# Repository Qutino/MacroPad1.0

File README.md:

# MacroPad1.1
This small macropad is the prototype with the intent of adding future improvements and iterating design further down the road.

Since this will be my first time building the supporting electronics around an ATMEGA32U4 microcontroller, 
as well as building and flashing the firmware from zero, a design with a smaller scope seemed like the best way to jump into things.

## Table of Contents
- [MacroPad1.1](#macropad11)
  - [Table of Contents](#table-of-contents)
  - [General Design Notes](#general-design-notes)
  - [Build Guide](#build-guide)
  - [Case Design Notes](#case-design-notes)
  - [Parts Notes](#parts-notes)
    - [HTML BOM](#html-bom)
    - [1. MCU](#1-mcu)
    - [2. Mini USB Connector](#2-mini-usb-connector)
    - [3. Fuse](#3-fuse)
    - [4. Capacitors](#4-capacitors)
    - [5. Resistors](#5-resistors)
    - [6. Reset Switch](#6-reset-switch)
    - [7. Crystal Oscillator](#7-crystal-oscillator)
    - [8. Diodes](#8-diodes)
  - [PCB Design Notes](#pcb-design-notes)
    - [Schematic](#schematic)
      - [Decoupling Capacitors](#decoupling-capacitors)
      - [Diode Matrix](#diode-matrix)
      - [Crystal Oscillator](#crystal-oscillator)
    - [Layout](#layout)
      - [Layer Count](#layer-count)
      - [Laying Traces](#laying-traces)
      - [USB Traces](#usb-traces)
      - [Decoupling capacitors](#decoupling-capacitors-1)
      - [Grounding mask](#grounding-mask)
      - [Crystal Placement](#crystal-placement)
    - [Production](#production)
      - [Surface Finish](#surface-finish)
      - [MFR](#mfr)
  - [Firmware](#firmware)
  - [Future Improvements](#future-improvements)

## General Design Notes

- Switches
  - This macropad will house 6 mechanical keyswitches, typical MX style and size.
- Dimensions
  - The PCB is 76.66mm x 42.86mm (LxW) with a notch protruding for the USB connector
  - For case designers, more detailed dimensions can be found [Here](KiCad/MacroPad1.0/MacroPad1.1_dims0.pdf) in the KiCad folder.
- Mounting
  - No holes in the PCB means the design is reliant on the plate be the main mounting structure. Either using screw holes or a sandwiched gasket mount design.
  - This is usually preferred in order to decrease the mechanical stress on the PCB itself during operation.
  - Next time include at least *one* hole in the PCB, for emergencies.
- MCU
  - ATMEGA32U4-AUR Microcontroller
  - This variant is actually rather large. for the next iteration thinking about going with the smaller MU variant, which comes in a VQFN package, 7x7mm. This will be more challenging to solder, especially without hot air or solder paste.
- USB Connection
  - Mini USB Connector
  - This is the easiest USB connector to hand solder, due to the size of the pins. good for a first prototype, but I'd like to move toward a more modern connector ASAP.
- Current protection
  - 500mA fuse
- Voltage protection
  - None, reverse voltage protection may have been a good add...

## Build Guide
- I'll create a step by step guide in a different doc soon!

## Case Design Notes
- Coming soon

## Parts Notes

### [HTML BOM](KiCad/MacroPad1.0/bom/MacroPad1.1-BOM.html)

### 1. MCU
  - [ATMEGA32U4-AUR](https://www.digikey.com/en/products/detail/microchip-technology/ATMEGA32U4-AUR/2238241)
  - 44 TQFP Package (10x10mm)
  - easy to solder
    
### 2. Mini USB Connector
  - Molex [0548190589](https://www.digikey.com/en/products/detail/molex/0548190589/2421468)
  - CONN RCPT MINI USB B 5POS SMD RA
  - 5 pin USB, easy to solder

### 3. Fuse
  - [Bel Fuse Inc. C1F 500](https://www.digikey.com/en/products/detail/bel-fuse-inc/C1F-500/4968258)
  - 1206 SMD
  - 500mA fast acting
### 4. Capacitors
  -  0805 SMD
  - 10uF, 0.1uF, 1uF, ~14pF
  - The values marked for C2 and C3 in the HTML BOM are incorrect. if not already updated, these should be replaced with 14pF capacitors. More details in the Crystal section.
### 5. Resistors
  - 0805 SMD
  - 10k: pu/pd resistors
  - 22ohm: USB datalines tx/rx.
### 6. Reset Switch
  - [PTS526 SK15 SMTR2 LFS](https://www.digikey.com/en/products/detail/c-k/PTS526-SK15-SMTR2-LFS/10056626)
  - SPST switch
  - low profile, nice form factor
### 7. Crystal Oscillator
  - [ECS-160-9-33B-CWN-TR](https://www.digikey.com/en/products/detail/ecs-inc/ECS-160-9-33B-CWN-TR/12349449)
  - 16MHz
  - Fragile, be careful when soldering! Use hot air + solder paste if available.
  - Pinout
    - There is a chamfer on the one of the pads underneath the crystal. This identifies pad #1. 
    - Pads #1 and #3 are connected to the two sides of the crystal. Pads #2 and #4 are bonded to the top metal lid and grounded.
  - Orientation
    - According to the layout, pad #1 will correspond to the bottom left pad on the pcb, on the side closest to C2.
    - The crystal is Bidirectional though, so dont worry too much about this.
### 8. Diodes
  - [1N4448W](https://www.digikey.com/en/products/detail/micro-commercial-co/1N4448W-TP/789330)
  - SOD-123 Package
  - fast switching

## PCB Design Notes

### Schematic

#### Decoupling Capacitors
- 0.1uF and 10uF decoupling capacitors are used to remove unwanted power distortion.

#### Diode Matrix
- This design implements a Diode Matrix to determine the keystrokes seen by the microcontroller.
- The Diode Matrix is what allows keyboards with 100+ keys to communicate individual keystrokes. By defining rows and columns and assigning each one to a different i/o port on the microcontroller, we can increase the number of discernable inputs to the microcontroller.
- For this board in particular, I could have mapped each Keyswitch to an individual pin on the MCU, but as more switches and features get added, we'll rapidly run out of space.
- So it's best to get used to using this early on!

#### Crystal Oscillator
- Load Capacitance: 9pF
    - The circuit was originally designed with incorrect values (1uF) chosen for the load capacitors. 
    - we can use the following equation to determine the correct values for the external load capacitors for a parallel resonant crystal.

$$ C_L = (C_{x1}*C_{x2})/(C_{x1} + C_{x2}) + C_{stray} $$

$$C_{x1} = C_{x2}$$

$$ C_x = 2(C_L - C_{stray}) $$

$$ C_L = 9pF, C_{stray} = 2pF$$

$$ \therefore C_x = 14pF$$

- Assuming a stray capacitance of 2pF, our resulting Load Capacitors C2 and C3 should be around **14pF**. (quite a lot lower than 1uF xd)
### Layout

- Initial layout:

- After optimization & improvements:
  - Slightly smaller footprint
  - Better USB Dataline routing
  - no mounting holes LOL
  - Grounding mask

#### Layer Count
- Just using a 2 layer design here, it's a simple enough design that it doesn't really require much more
- Griff recommends four layer, lets try that next time.

#### Laying Traces
- Generally speaking, I tend to like putting horizontal traces on the front side, and vertical traces on the back side of the PCB (or vice versa), connecting with vias where necessary.

#### USB Traces
- USB datalines should be parallel at all times.
- 45 degree angles for traces whenever possible, sharp corners could impact signal integrity.
- I should also have tried to avoid using vias for the USB datalines, since I've read that incorrect use could cause signal reflection and attenuation. No issues so far though!

#### Decoupling capacitors
- Placement and trace routing is important!

#### Grounding mask
- Added Grounding mask around USB, MCU, and Crystal area. 
- none around switches since that shouldn't be an area that would attract too much unwanted noise. Re-assess if possible.

#### Crystal Placement
- Crystal placed as close as reasonably possible to the XTAL pins on the MCU.
- Took care to also place Load capacitors as close to the crystal as possible.
- Long copper traces could interfere with the crystal clock. Undesirable.

### Production

#### Surface Finish
- Lead-free HASL. ENIG would have been pretty, but it's too expensive.

#### MFR
- Produced by JLCPCB, very afforable. Might consider factory population at some point.

## Firmware
- documentation coming soon

## Future Improvements
In order of most to least likely to implement

  1. More switches
  2. Hotswap sockets
  3. Power Indication LED
  5. Rotary encoder
  6. smaller MCU form factor, either VQFN ATmega32u4-MUR, or RP2040
  7. USB C connector, or at least micro USB
  8. RGB
  9. OLED display
  10. Through hole style Crystal Oscillator for easier soldering? low priority, since a smaller MCU will also be difficult to solder
  11. Bluetooth?? + Battery??

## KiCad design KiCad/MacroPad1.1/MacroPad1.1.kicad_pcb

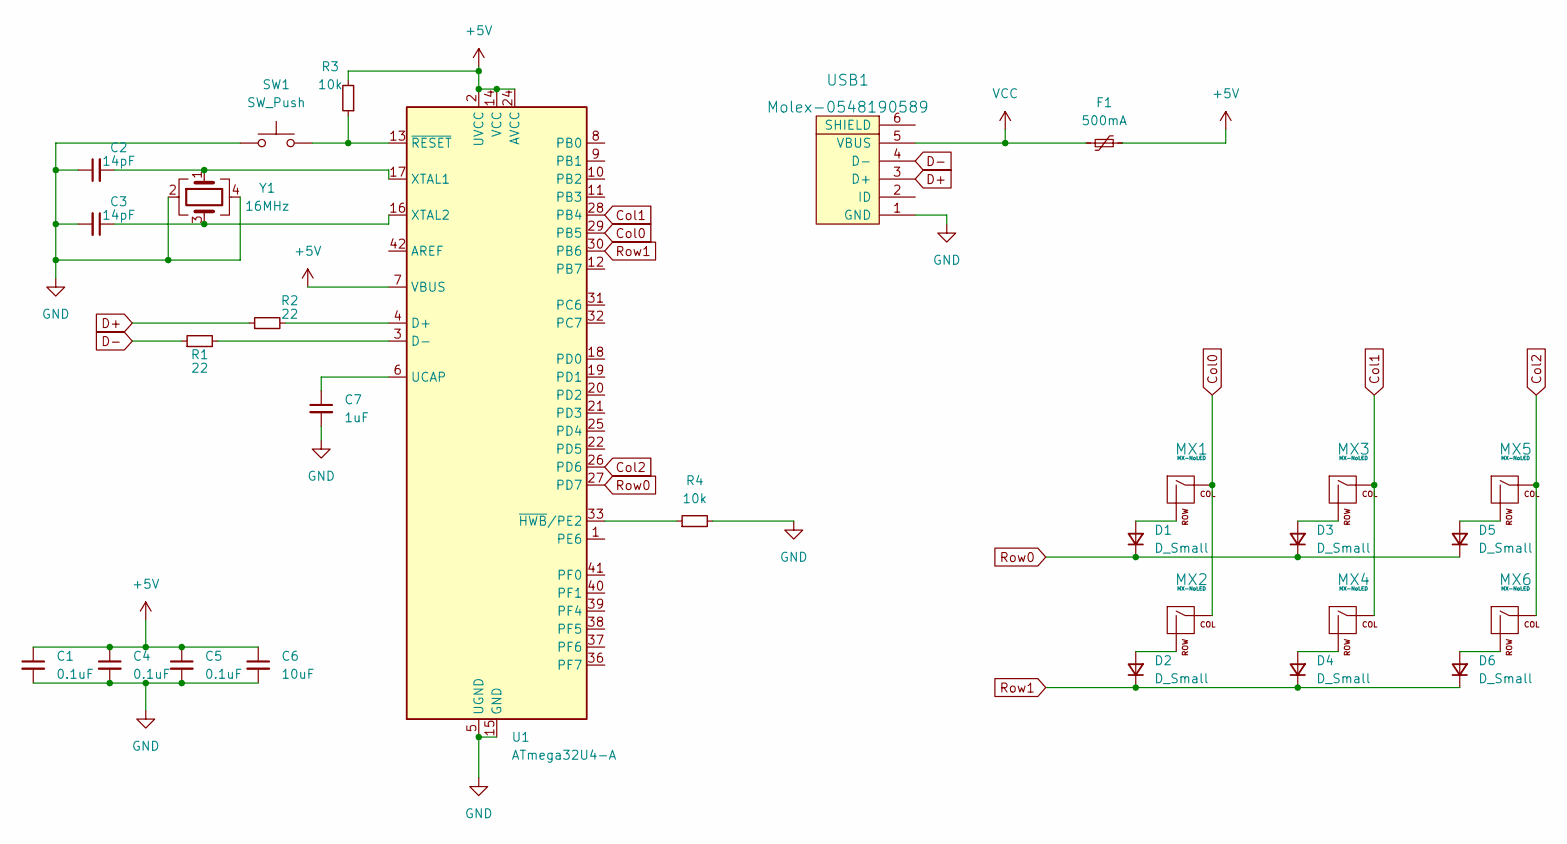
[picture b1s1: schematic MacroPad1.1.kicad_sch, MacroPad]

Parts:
C1, C4, C5: 0.1uF; C_0805_2012Metric
C2, C3: 14pF; C_0805_2012Metric
C6: 10uF; C_0805_2012Metric
C7: 1uF; C_0805_2012Metric
D1, D2, D3, D4, D5, D6: D_Small; D_SOD-123
F1: 500mA; Fuse_1206_3216Metric
MX1, MX2, MX3, MX4, MX5, MX6: MX-NoLED; MX-1U-NoLED
R1, R2: 22; R_0805_2012Metric
R3, R4: 10k; R_0805_2012Metric
SW1: SW_Push; SKQG-1155865
U1: ATmega32U4-A; TQFP-44_10x10mm_P0.8mm
USB1: Molex-0548190589
Y1: 16MHz; Crystal_SMD_3225-4Pin_3.2x2.5mm

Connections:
+5V: C1.1, C4.1, C5.1, C6.1, F1.2, R3.2, U1.2 (UVCC), U1.7 (VBUS), U1.14 (VCC), U1.24 (AVCC), U1.34 (VCC), U1.44 (AVCC)
Col0: MX1.1 (COL), MX2.1 (COL), U1.29 (PB5)
Col1: MX3.1 (COL), MX4.1 (COL), U1.28 (PB4)
Col2: MX5.1 (COL), MX6.1 (COL), U1.26 (PD6)
D+: R2.1, USB1.3 (D+)
D-: R1.1, USB1.4 (D-)
GND: C1.2, C2.1, C3.2, C4.2, C5.2, C6.2, C7.2, R4.2, SW1.1, U1.5 (UGND), U1.15 (GND), U1.23 (GND), U1.35 (GND), U1.43 (GND), USB1.1 (GND), Y1.2, Y1.4
unnamed: C2.2, U1.17 (XTAL1), Y1.1
unnamed: C3.1, U1.16 (XTAL2), Y1.3
unnamed: C7.1, U1.6 (UCAP)
unnamed: D1.2 (A), MX1.2 (ROW)
unnamed: D2.2 (A), MX2.2 (ROW)
unnamed: D3.2 (A), MX3.2 (ROW)
unnamed: D4.2 (A), MX4.2 (ROW)
unnamed: D5.2 (A), MX5.2 (ROW)
unnamed: D6.2 (A), MX6.2 (ROW)
unnamed: R1.2, U1.3 (D-)
unnamed: R2.2, U1.4 (D+)
unnamed: R3.1, SW1.2, U1.13 (~RESET)
unnamed: R4.1, U1.33 (~HWB/PE2)
Row0: D1.1 (K), D3.1 (K), D5.1 (K), U1.27 (PD7)
Row1: D2.1 (K), D4.1 (K), D6.1 (K), U1.30 (PB6)
VCC: F1.1, USB1.5 (VBUS)

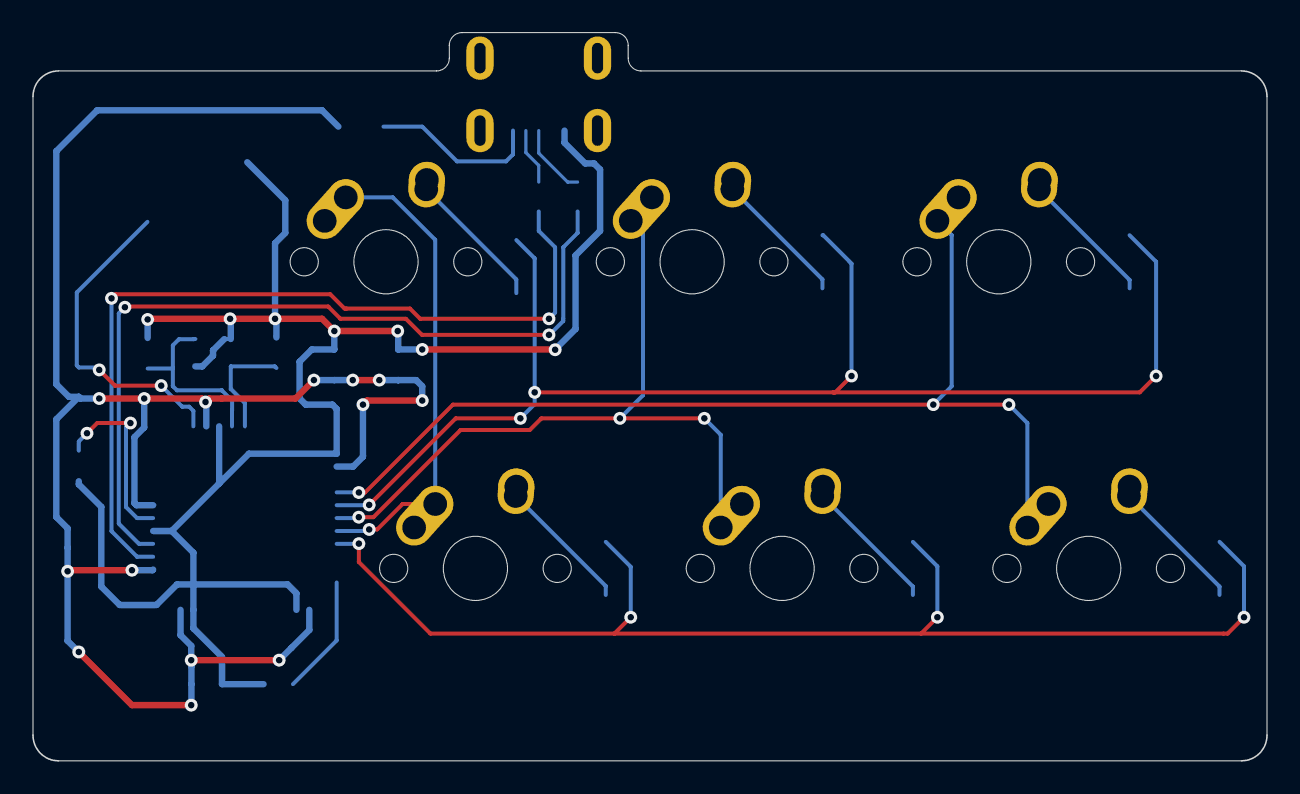
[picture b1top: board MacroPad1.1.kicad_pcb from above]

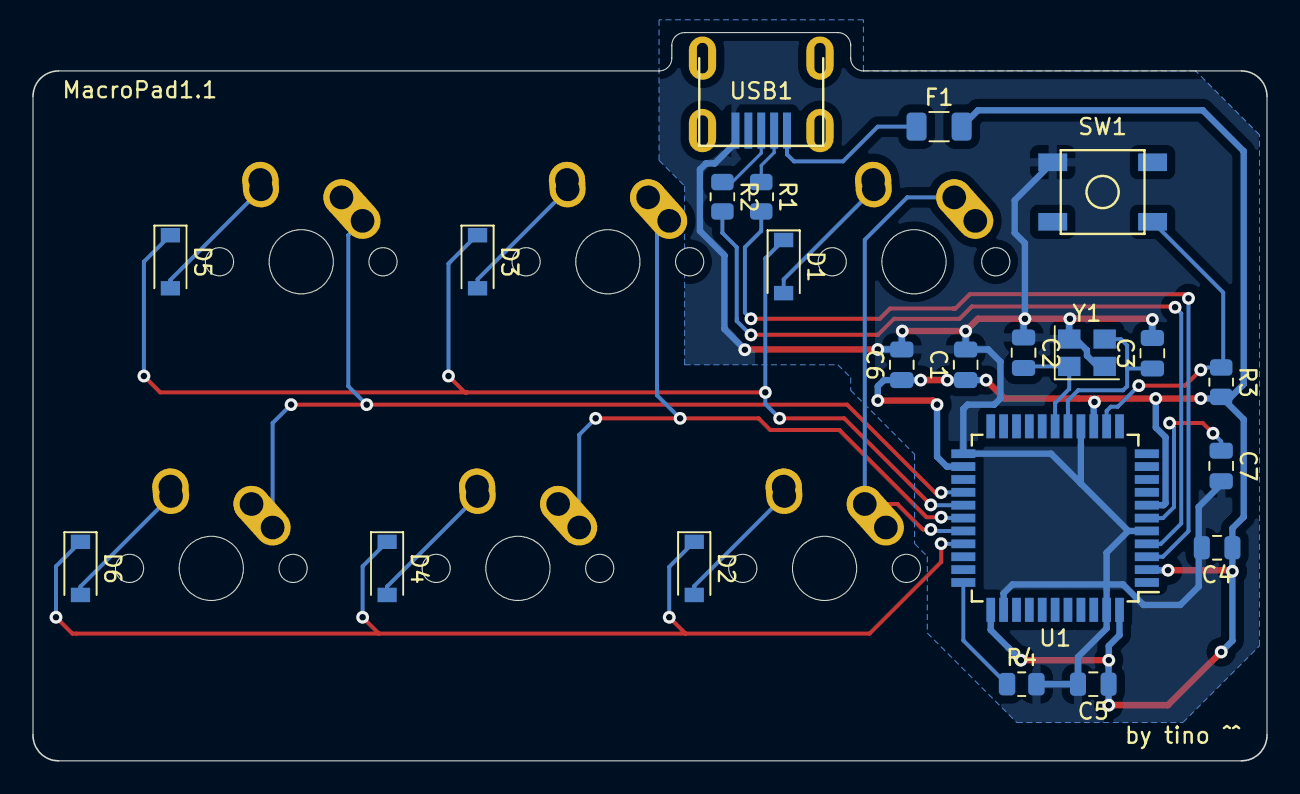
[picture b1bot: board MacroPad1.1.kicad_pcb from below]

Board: 2 copper layers, 76.7 x 45.2 mm, 28 parts (22 on the bottom side), 23 nets.

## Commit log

2023-05-23 Add MIT License
    Added MIT License to repo
2023-05-24 Created KiCad Project
2023-05-25 Added MCU Schematic
    Wiring for ATMEGA32U4
2023-05-25 Added USB and Switches
2023-05-25 Assigned Footprints
2023-05-27 PCB Layout complete
2023-05-27 PCB traces complete
2023-05-27 Added ground mask & screenshot
2023-05-27 Adjusted Traces
2023-05-27 Added Gerber files
2023-05-27 auto backup
2023-05-27 autobackup
2023-05-29 New PCB Layout, shrunk by 20mm
2023-05-31 Added ground mask
2023-06-01 Adjusted page size
    and also rearranged symbols
2023-06-01 backup created
2023-06-11 Created dimension pdf
2023-08-30 Large-ish update
    - added firmware .hex file!
    - updated readme.md with intent and design
    - added interactive HTML BOM
2023-08-30 Update README.md
    minor wording
2023-09-02 added firmware files
2023-09-03 Documentation Update
    Massive Update with design notes, images, thought processes, potential future improvements, and more.
2023-09-03 Fixed crystal load capacitance equation
    Syntax and description updtes
2023-09-03 Documentation Updates
    Updated HTML BOM, small additions to README
2023-09-03 Clearing backups
2023-09-11 Update README.md
    Added items to future improvements section.
2023-09-12 Removed files
2023-09-30 added new media firmware file
2024-10-25 added Schematic Screenshot
2024-10-25 Added New Version Folder
